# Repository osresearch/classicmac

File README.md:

Classic Mac CRT Interface
=========================

Mac 128/Plus/SE hardware interface using the BeagleBone Black PRU.

Run the virtual frame buffer:

	Xvfb :0 -ac -screen 0 512x384x8 -fbdir /tmp/ -retro

Start the X11 to Mac CRT translation:

	./x11mac /tmp/Xvfb_screen0

And start the mouse/keyboard event to X11 event translation:

	./eventmap /dev/input/event*

Problems?  hudson@trmm.net

When HSYNC is low, force VIDEO high.

H V
0 0 1
0 1 1
1 0 1
1 1 0

!(HV)

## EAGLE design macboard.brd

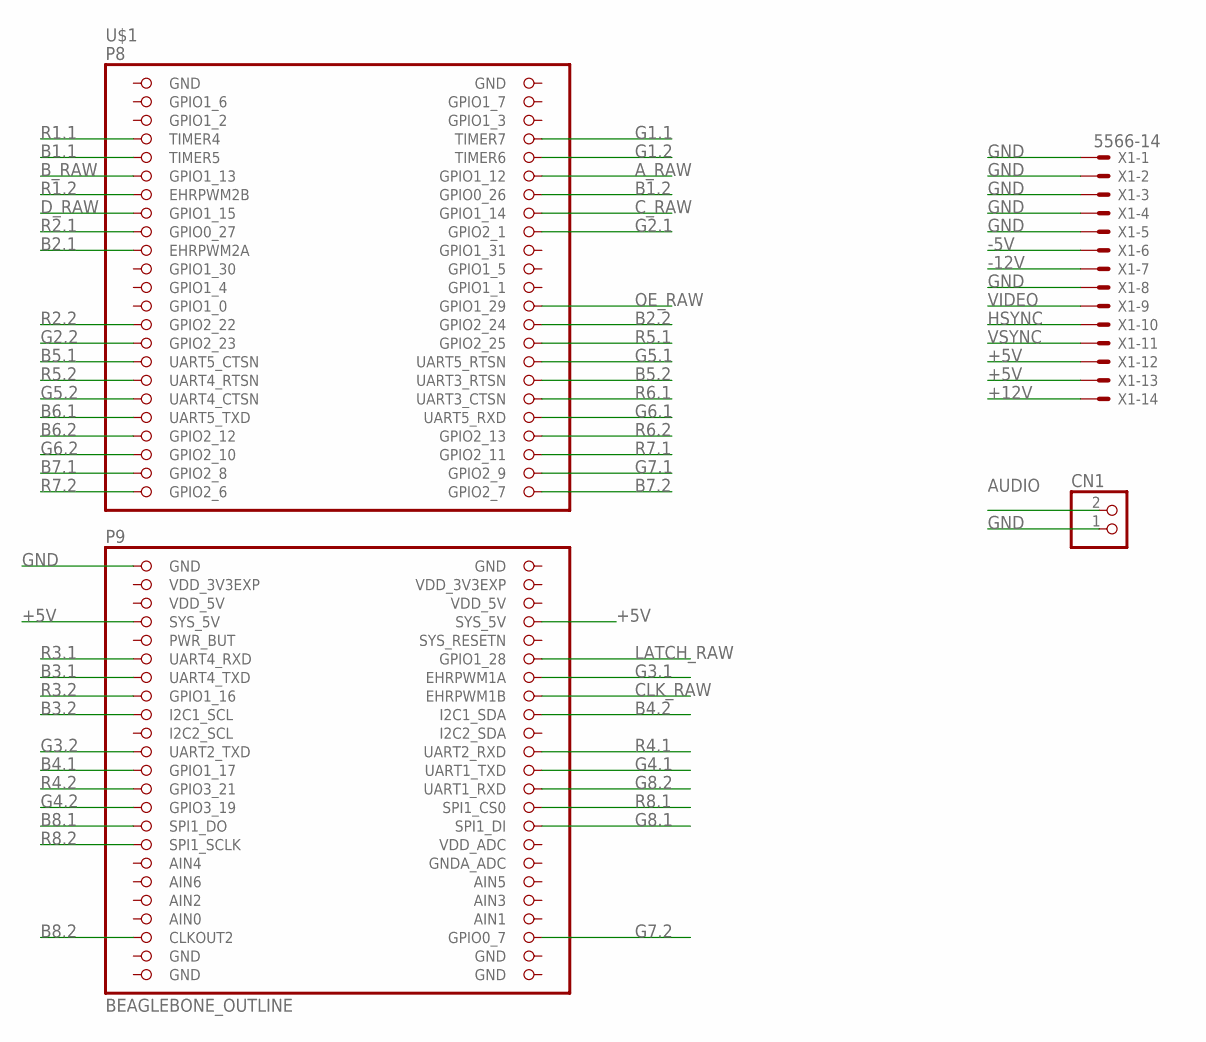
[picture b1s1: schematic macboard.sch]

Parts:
CN1: JST_2PIN-THM; JST-PH-2-THM
U$1: BEAGLEBONE_OUTLINE; BEAGLEBONE_SHIELD
X1: 5566-14

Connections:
+5V: U$1.53 (SYS_5V), U$1.54 (SYS_5V), X1.12, X1.13
+12V: X1.14
-5V: X1.6
-12V: X1.7
AIN0: U$1.85 (AIN0)
AUDIO: CN1.2 (1)
A_RAW: U$1.12 (GPIO1_12)
B1.1: U$1.9 (TIMER5)
B1.2: U$1.14 (GPIO0_26)
B2.1: U$1.19 (EHRPWM2A)
B2.2: U$1.28 (GPIO2_24)
B3.1: U$1.59 (UART4_TXD)
B3.2: U$1.63 (I2C1_SCL)
B4.1: U$1.69 (GPIO1_17)
B4.2: U$1.64 (I2C1_SDA)
B5.1: U$1.31 (UART5_CTSN)
B5.2: U$1.34 (UART3_RTSN)
B6.1: U$1.37 (UART5_TXD)
B6.2: U$1.39 (GPIO2_12)
B7.1: U$1.43 (GPIO2_8)
B7.2: U$1.46 (GPIO2_7)
B8.1: U$1.75 (SPI1_DO)
B8.2: U$1.87 (CLKOUT2)
B_RAW: U$1.11 (GPIO1_13)
CLK_RAW: U$1.62 (EHRPWM1B)
C_RAW: U$1.16 (GPIO1_14)
D_RAW: U$1.15 (GPIO1_15)
G1.1: U$1.8 (TIMER7)
G1.2: U$1.10 (TIMER6)
G2.1: U$1.18 (GPIO2_1)
G2.2: U$1.29 (GPIO2_23)
G3.1: U$1.60 (EHRPWM1A)
G3.2: U$1.67 (UART2_TXD)
G4.1: U$1.70 (UART1_TXD)
G4.2: U$1.73 (GPIO3_19)
G5.1: U$1.32 (UART5_RTSN)
G5.2: U$1.35 (UART4_CTSN)
G6.1: U$1.38 (UART5_RXD)
G6.2: U$1.41 (GPIO2_10)
G7.1: U$1.44 (GPIO2_9)
G7.2: U$1.88 (GPIO0_7)
G8.1: U$1.76 (SPI1_DI)
G8.2: U$1.72 (UART1_RXD)
GND: CN1.1 (2), U$1.1 (GND), U$1.2 (GND), U$1.47 (GND), U$1.48 (GND), U$1.89 (GND), U$1.90 (GND), U$1.91 (GND), U$1.92 (GND), X1.1, X1.2, X1.3, X1.4, X1.5, X1.8
HSYNC: X1.10
LATCH_RAW: U$1.58 (GPIO1_28)
OE_RAW: U$1.26 (GPIO1_29)
R1.1: U$1.7 (TIMER4)
R1.2: U$1.13 (EHRPWM2B)
R2.1: U$1.17 (GPIO0_27)
R2.2: U$1.27 (GPIO2_22)
R3.1: U$1.57 (UART4_RXD)
R3.2: U$1.61 (GPIO1_16)
R4.1: U$1.68 (UART2_RXD)
R4.2: U$1.71 (GPIO3_21)
R5.1: U$1.30 (GPIO2_25)
R5.2: U$1.33 (UART4_RTSN)
R6.1: U$1.36 (UART3_CTSN)
R6.2: U$1.40 (GPIO2_13)
R7.1: U$1.42 (GPIO2_11)
R7.2: U$1.45 (GPIO2_6)
R8.1: U$1.74 (SPI1_CS0)
R8.2: U$1.77 (SPI1_SCLK)
VDD_3V3EXP: U$1.49 (VDD_3V3EXP), U$1.50 (VDD_3V3EXP)
VDD_5V: U$1.51 (VDD_5V), U$1.52 (VDD_5V)
VIDEO: X1.9
VSYNC: X1.11

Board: 2 copper layers, 3 parts (0 on the bottom side), 4 nets, no tracks yet.

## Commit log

2013-12-18 Tweak timings
2014-01-26 copied from old LEDscape tree
2014-01-26 extracted from LEDscape tree, tied to old build system
2014-01-26 ignore more files
2014-01-26 fixed register boundary crossing lines, hsync now is visible
2014-01-26 reduce dot crawl by checking remainder of timer
2014-01-26 more timer tweaks to try to reduce banding; still some jitter
2014-01-26 switched pins around
2014-01-26 almost works to read the Xvfb data
2014-01-26 better fb_copy(), but still offset by 256?
2014-01-26 almost works; still off by a few pixels
2014-01-28 eventmapping works!
2014-01-28 Try a delay after VSYNC falling edge before HSYNC falls
2014-01-28 start script for xvfb
2014-01-28 hardcoded offset works, but meh
2014-01-28 eventmap handles the mouse
2014-01-28 eventmap works for keyboard and mouse
2014-01-28 Startup "instructions"
2014-01-28 30usec, not 3usec per frame
2014-01-28 note that there are still problems
2014-01-28 Started on PCB for adapter board; need to add ADB and power poles
2014-01-28 audio
2014-01-29 turn on eventmap too
2014-01-29 x colormap fixes; looks good!
2014-02-01 use the LCD interface to drive the Mac display (with external NOT gate)
2014-02-01 rename to keep it short
2014-02-01 even shorter
2014-02-01 works with NAND gate on VIDEO and HSYNC, but shifted to the right
2014-02-01 Remove extra cruft from dts
2014-02-08 started on adb interface using a teensy 2.0
2014-02-08 poll devices; not reading reliably yet
2014-02-08 looks like reading on falling edge is working
2014-02-09 mouse event decoding appears to work
2014-02-09 built keymap
2014-02-09 keymap translation almost works, except for specials
2014-02-09 adb keyboard works! with modifiers since Keyboard.press() takes a uint16_t
